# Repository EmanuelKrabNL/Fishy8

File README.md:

# Fishy8
PCB with vintage camera looking footage. A microphone and a fisheye lens.

Okay, name explained first
FISHeYe lens + hi8 = FISHY8!
Original name was FISH8 but FISHY8 sounds more jolly.

## Why have i made this?
Those old sony handycams are increndibly hard to get. Except if you live near the old camera market in barcelona (I still hate that it wasnt open when i was there.), so, why not make one that costs a one time payment of max 120 bucks, and doesnt require extra additions like those 100 dollar converters. but has a 15 dollar converter inside of it! SSo its basically an old camcorder replacement, that i made myself! 
## What does it do?

The caddx ratel 2 (camera), is analog, thus producing cvbs footage. If we add a cvbs to usb c converter, we can make it 'act' like a webcam, and get that old, fissheye looking footage directly on our phone!

## Disclaimer:
this project does not require any firmware, and gets over the 30 dollar limit. I will pay for it with my own money, therefore, the 30 bucks will help, but it wont be enough.

## How to use it?
Well, basically just put all the cables where they belong (lol), use another usbc - usbc cable to plug your phone into the gracetop converter, and then use an external android camera app that can detect other sources to acutally film the footage.
The included 'joystick', can control if you want your video to be ntsc or pal, and other on screen information, like time etc.

## BOM
For the Bom file, please go here!
Read the [Bom file](Bom.csv) for this project.

(I dont really know how to link files, but i think it needs to be done like this)

I got a fpv camera with fisheye built in, for easyness: footage looks like this:

so, allat of yap. what does it look like?

PCB

SCHEMATIC

3D

ehh not the pretties, but gets the job done LOL!

I am planning to make a 3d print later on, zo the additional components can snap on!
It doesnt need any firmware, since android supports the gracetop cvbs to usb c natively.

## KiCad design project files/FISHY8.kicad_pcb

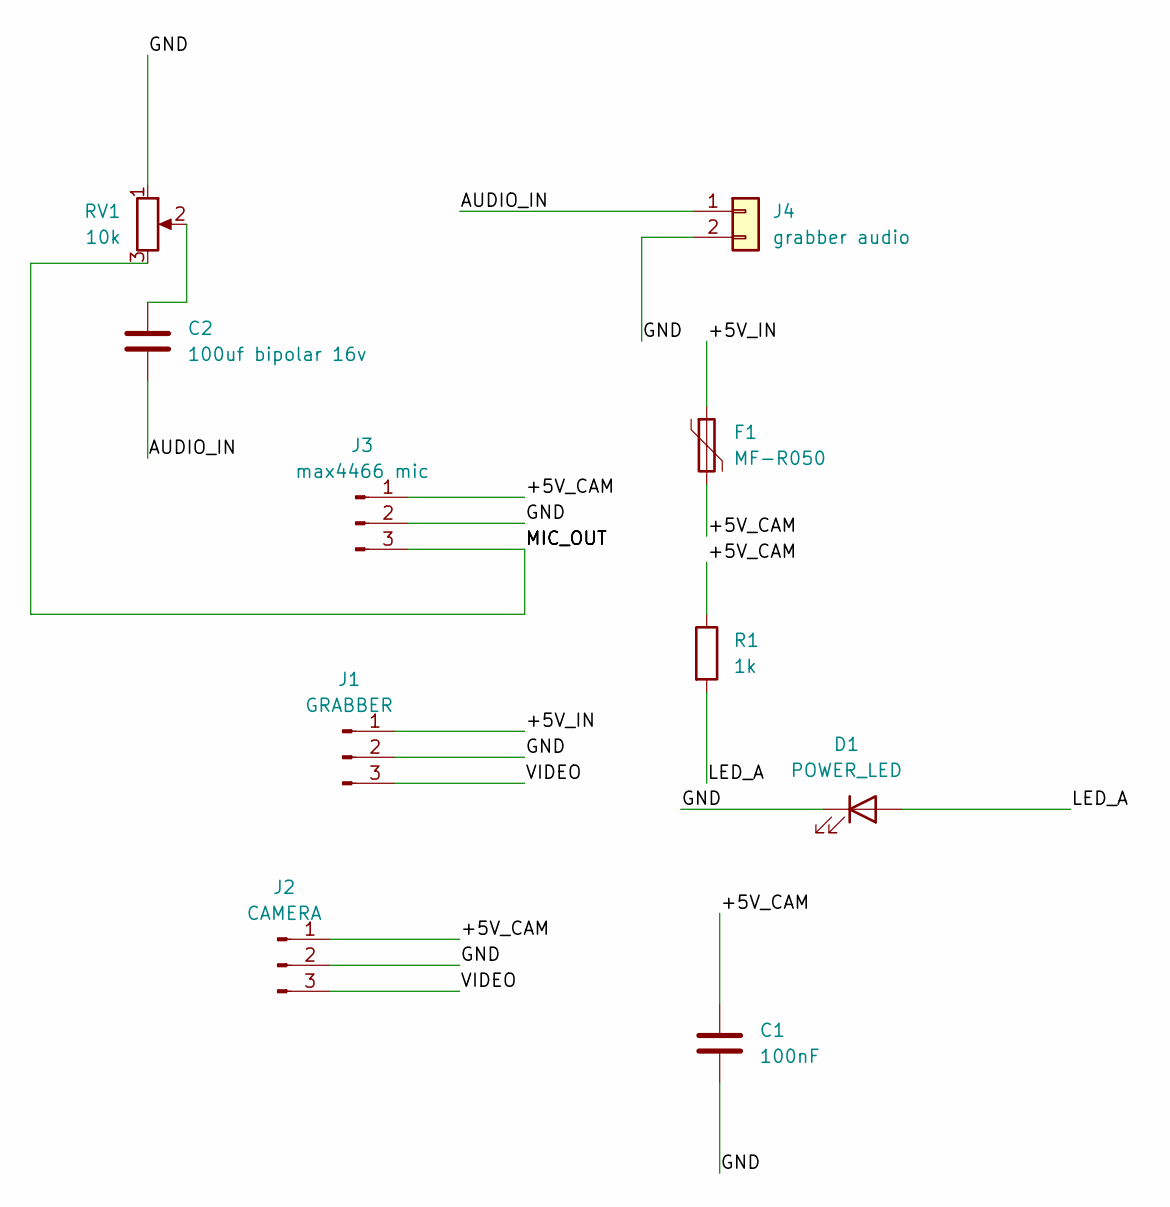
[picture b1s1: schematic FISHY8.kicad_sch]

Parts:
C1: 100nF; C_Vishay_K104K15X7RF5TH5_P5.00
C2: 100uf bipolar 16v; C_Radial_D10.0mm_H12.5mm_P5.00mm
D1: POWER_LED; LED_Kingbright_L934ID_TNB2.54_P2.54_Drill1.20
F1: MF-R050; MF_R050_P5.10
J1: GRABBER; WirePads_1x03_P2.54
J2: CAMERA; WirePads_1x03_P2.54
J3: max4466 mic; PinSocket_1x03_P2.54mm_Vertical
J4: grabber audio; PinHeader_1x02_P2.54mm_Vertical
R1: 1k; R_Axial_DIN0207_L6.3mm_D2.5mm_P10.16mm_Horizontal
RV1: 10k; Potentiometer_Bourns_3296W_Vertical

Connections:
/+5V_CAM: C1.1, F1.2, J2.1, J3.1, R1.1
/+5V_IN: F1.1, J1.1
/AUDIO_IN: C2.2, J4.1
/GND: C1.2, D1.1 (K), J1.2, J2.2, J3.2, J4.2, RV1.1
/LED_A: D1.2 (A), R1.2
/MIC_OUT: J3.3, RV1.3
/VIDEO: J1.3, J2.3
unnamed: C2.1, RV1.2

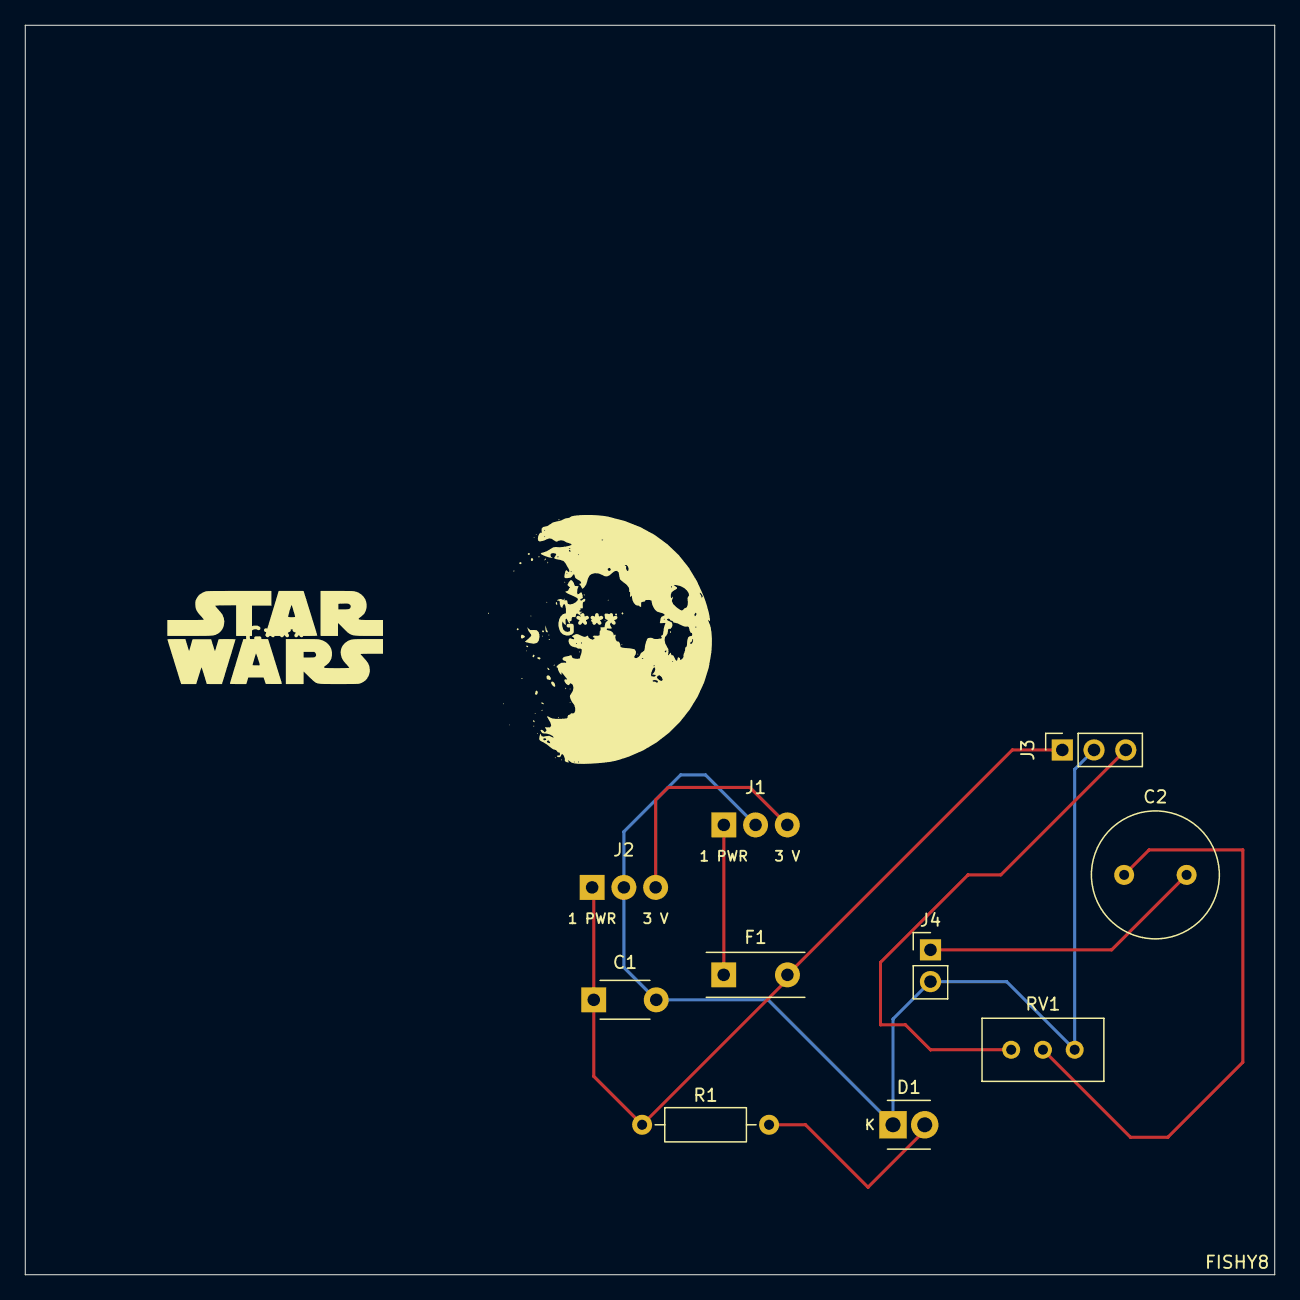
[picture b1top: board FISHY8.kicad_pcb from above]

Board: 2 copper layers, 100.0 x 100.0 mm, 13 parts (0 on the bottom side), 8 nets.

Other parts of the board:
M1: 30x30, actual cam is 19x19; RESERVE_CAMERA_30x30_MEASURE_FIRST
M2: 55x30 unmeasured; RESERVE_GRABBER_55x30_MEASURE_FIRST
M3: 35x35 screen devise joystick thang; RESERVE_OSD_35x35_MEASURE_FIRST
